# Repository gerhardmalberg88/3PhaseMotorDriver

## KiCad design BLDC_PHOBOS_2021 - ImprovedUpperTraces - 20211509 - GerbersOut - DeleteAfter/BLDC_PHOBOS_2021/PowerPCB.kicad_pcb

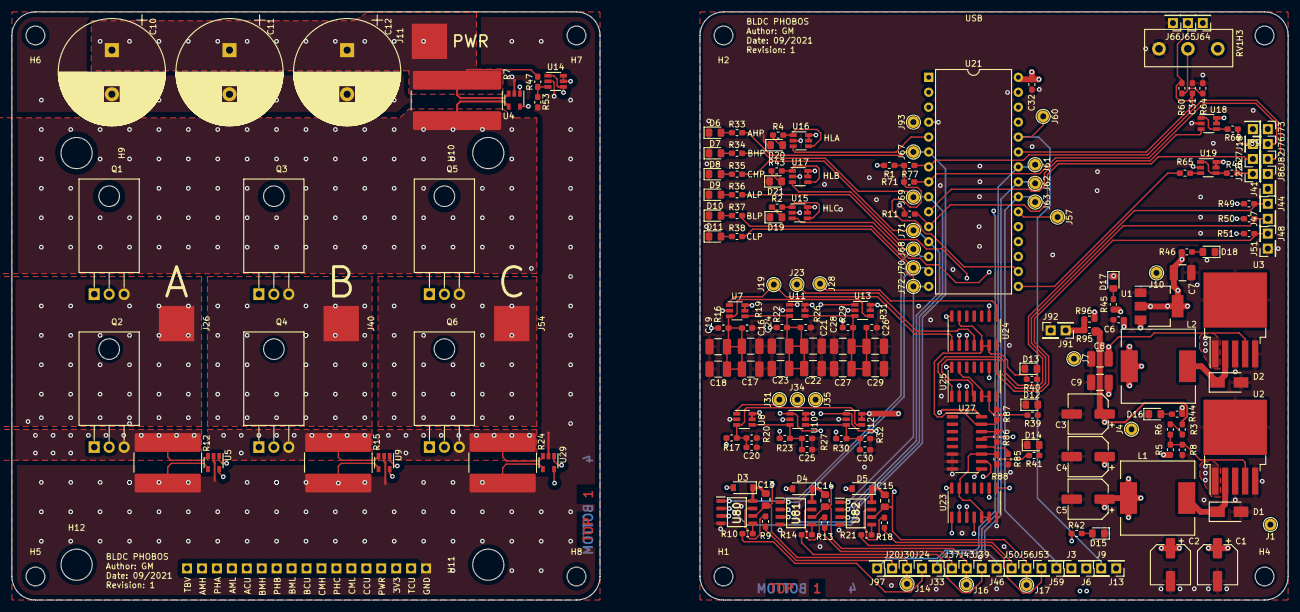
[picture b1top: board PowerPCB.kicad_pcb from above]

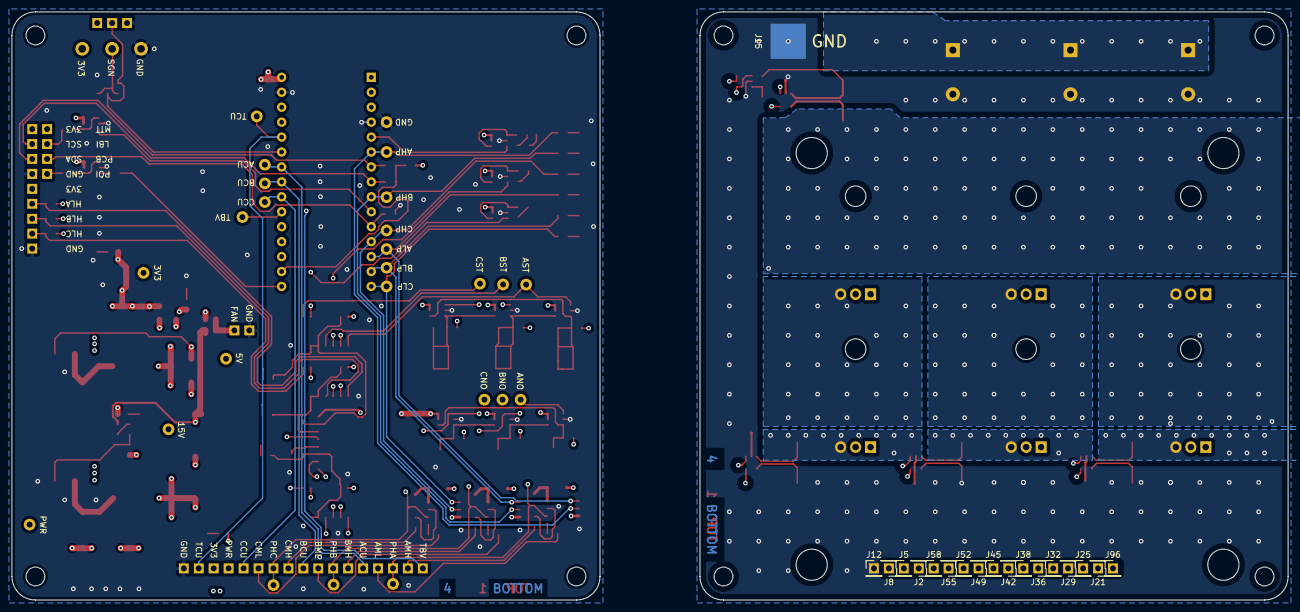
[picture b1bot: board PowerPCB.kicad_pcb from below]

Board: 4 copper layers, 100.0 x 100.0 mm, 245 parts (18 on the bottom side), 116 nets.

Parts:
C1, C2, C3, C4, C5: 100uF; CP_Elec_6.3x5.3
C6, C20, C25, C30, C31, C32: 100nF; C_0603_1608Metric_Pad1.05x0.95mm_HandSolder
C7, C8, C9, C16, C17, C18, C19, C21, C22, C23, C24, C26, C27, C28, C29: 47uF; C_1210_3225Metric_Pad1.42x2.65mm_HandSolder
C10, C11, C12: 1000uF; CP_Radial_D18.0mm_P7.50mm
C13, C14, C15: 1uF; C_0805_2012Metric_Pad1.15x1.40mm_HandSolder
D1, D2: 1A; D_SMA
D3, D4, D5: D_ALT; D_SOD-123
D6: LED_A_HIGH; LED_0805_2012Metric_Pad1.15x1.40mm_HandSolder
D7: LED_B_HIGH; LED_0805_2012Metric_Pad1.15x1.40mm_HandSolder
D8: LED_C_HIGH; LED_0805_2012Metric_Pad1.15x1.40mm_HandSolder
D9: LED_A_LOW; LED_0805_2012Metric_Pad1.15x1.40mm_HandSolder
D10: LED_B_LOW; LED_0805_2012Metric_Pad1.15x1.40mm_HandSolder
D11: LED_C_LOW; LED_0805_2012Metric_Pad1.15x1.40mm_HandSolder
D12: HALL_DATA_CONTROL; LED_0805_2012Metric_Pad1.15x1.40mm_HandSolder
D13: BEMF_START_DATA_CONTROL; LED_0805_2012Metric_Pad1.15x1.40mm_HandSolder
D14: BEMF_NORMAL_DATA_CONTROL; LED_0805_2012Metric_Pad1.15x1.40mm_HandSolder
D15: +48V LED; LED_0805_2012Metric_Pad1.15x1.40mm_HandSolder
D16: +12V LED; LED_0805_2012Metric_Pad1.15x1.40mm_HandSolder
D17: +5V LED; LED_0805_2012Metric_Pad1.15x1.40mm_HandSolder
D18: +3V3 LED; LED_0805_2012Metric_Pad1.15x1.40mm_HandSolder
D19, D20, D21: LED_HALL_BEMF; LED_0805_2012Metric_Pad1.15x1.40mm_HandSolder
H1, H2, H3, H4, H5, H6, H7, H8: MountingHole; MountingHole_3.2mm_M3
H9, H10, H11, H12: MountingHole; MountingHole_5.3mm_M5
J1: POWER+; TestPoint_THTPad_D2.0mm_Drill1.0mm
J2: 48V_From_PowerPCB; PinHeader_1x01_P2.54mm_Vertical
J3: 48V_to_Control_PCB; PinHeader_1x01_P2.54mm_Vertical
J4: +15V External; TestPoint_THTPad_D2.0mm_Drill1.0mm
J5: +3V3PowerPCB; PinHeader_1x01_P2.54mm_Vertical
J6: +3V3ControlPCB; PinHeader_1x01_P2.54mm_Vertical
J7: +5V External; TestPoint_THTPad_D2.0mm_Drill1.0mm
J8: Total_Current_Differential_PowerPCB; PinHeader_1x01_P2.54mm_Vertical
J9: Total_Current_Differential_ControlPCB; PinHeader_1x01_P2.54mm_Vertical
J10: +3V3 External; TestPoint_THTPad_D2.0mm_Drill1.0mm
J11: Con_POWER_B+; Power_Pad_6x6mm
J12: CommonGND_PowerPCB; PinHeader_1x01_P2.54mm_Vertical
J13: CommonGND_ControlPCB; PinHeader_1x01_P2.54mm_Vertical
J14: Phase_A_RAW; TestPoint_THTPad_D2.0mm_Drill1.0mm
J15: Con_POWER_GND; Power_Pad_6x6mm
J16: Phase_B_RAW; TestPoint_THTPad_D2.0mm_Drill1.0mm
J17: Phase_C_RAW; TestPoint_THTPad_D2.0mm_Drill1.0mm
J18: Low_Battery_Voltage_Indicator_Output; PinHeader_1x01_P2.54mm_Vertical
J19: Phase_A_Zero_Filtered_Start; TestPoint_THTPad_D2.0mm_Drill1.0mm
J20: A_MOS_HIGH_ControlPCB; PinHeader_1x01_P2.54mm_Vertical
J21: A_MOS_HIGH_PowerPCB; PinHeader_1x01_P2.54mm_Vertical
J22: Power_ON_Indicator_Output; PinHeader_1x01_P2.54mm_Vertical
J23: Phase_B_Zero_Filtered_Start; TestPoint_THTPad_D2.0mm_Drill1.0mm
J24: A_MOS_LOW_ControlPCB; PinHeader_1x01_P2.54mm_Vertical
J25: Phase_A_PowerPCB; PinHeader_1x01_P2.54mm_Vertical
J26: Connector_A; Power_Pad_6x6mm
J27: Program&Control_Button; PinHeader_1x01_P2.54mm_Vertical
J28: Phase_C_Zero_Filtered_Start; TestPoint_THTPad_D2.0mm_Drill1.0mm
J29: A_MOS_LOW_PowerPCB; PinHeader_1x01_P2.54mm_Vertical
J30: Phase_A_ControlPCB; PinHeader_1x01_P2.54mm_Vertical
J31: Phase_A_Zero_Filtered_Normal; TestPoint_THTPad_D2.0mm_Drill1.0mm
J32: A_Shunt+_PowerPCB; PinHeader_1x01_P2.54mm_Vertical
J33: A_Shunt+_ControlPCB; PinHeader_1x01_P2.54mm_Vertical
J34: Phase_B_Zero_Filtered_Normal; TestPoint_THTPad_D2.0mm_Drill1.0mm
J35: Phase_C_Zero_Filtered_Normal; TestPoint_THTPad_D2.0mm_Drill1.0mm
J36: B_MOS_HIGH_PowerPCB; PinHeader_1x01_P2.54mm_Vertical
J37: B_MOS_HIGH_ControlPCB; PinHeader_1x01_P2.54mm_Vertical
J38: Phase_B_PowerPCB; PinHeader_1x01_P2.54mm_Vertical
J39: B_MOS_LOW_ControlPCB; PinHeader_1x01_P2.54mm_Vertical
J40: Connector_B; Power_Pad_6x6mm
J41: Hall +3V3; PinHeader_1x01_P2.54mm_Vertical
J42: B_MOS_LOW_PowerPCB; PinHeader_1x01_P2.54mm_Vertical
J43: Phase_B_ControlPCB; PinHeader_1x01_P2.54mm_Vertical
J44: Con_HALL_A; PinHeader_1x01_P2.54mm_Vertical
J45: B_Shunt+_PowerPCB; PinHeader_1x01_P2.54mm_Vertical
J46: B_Shunt+_ControlPCB; PinHeader_1x01_P2.54mm_Vertical
J47: Con_HALL_B; PinHeader_1x01_P2.54mm_Vertical
J48: Con_HALL_C; PinHeader_1x01_P2.54mm_Vertical
J49: C_MOS_HIGH_PowerPCB; PinHeader_1x01_P2.54mm_Vertical
J50: C_MOS_HIGH_ControlPCB; PinHeader_1x01_P2.54mm_Vertical
J51: Hall GND; PinHeader_1x01_P2.54mm_Vertical
J52: Phase_C_PowerPCB; PinHeader_1x01_P2.54mm_Vertical
J53: C_MOS_LOW_ControlPCB; PinHeader_1x01_P2.54mm_Vertical
J54: Connector_C; Power_Pad_6x6mm
J55: C_MOS_LOW_PowerPCB; PinHeader_1x01_P2.54mm_Vertical
J56: Phase_C_ControlPCB; PinHeader_1x01_P2.54mm_Vertical
J57: Voltage Sense SGN; TestPoint_THTPad_D2.0mm_Drill1.0mm
J58: C_Shunt+_PowerPCB; PinHeader_1x01_P2.54mm_Vertical
J59: C_Shunt+_ControlPCB; PinHeader_1x01_P2.54mm_Vertical
J60: Total_Battery_Current; TestPoint_THTPad_D2.0mm_Drill1.0mm
J61: A_Low_Side_Current_ADC; TestPoint_THTPad_D2.0mm_Drill1.0mm
J62: B_Low_Side_Current_ADC; TestPoint_THTPad_D2.0mm_Drill1.0mm
J63: C_Low_Side_Current_ADC; TestPoint_THTPad_D2.0mm_Drill1.0mm
J64: Throttle 3V3; PinHeader_1x01_P2.54mm_Vertical
J65: Throttle Signal; PinHeader_1x01_P2.54mm_Vertical
J66: Throttle GND; PinHeader_1x01_P2.54mm_Vertical
J67: A_HIGH_MCU; TestPoint_THTPad_D2.0mm_Drill1.0mm
J68: A_LOW_MCU; TestPoint_THTPad_D2.0mm_Drill1.0mm
J69: B_HIGH_MCU; TestPoint_THTPad_D2.0mm_Drill1.0mm
J70: B_LOW_MCU; TestPoint_THTPad_D2.0mm_Drill1.0mm
J71: C_HIGH_MCU; TestPoint_THTPad_D2.0mm_Drill1.0mm
J72: C_LOW_MCU; TestPoint_THTPad_D2.0mm_Drill1.0mm
J73: I2C 3V3; PinHeader_1x01_P2.54mm_Vertical
J76: I2C_SCL; PinHeader_1x01_P2.54mm_Vertical
J82: I2C_SDA; PinHeader_1x01_P2.54mm_Vertical
J86: I2C GND; PinHeader_1x01_P2.54mm_Vertical
J89: Motor_Temp; PinHeader_1x01_P2.54mm_Vertical
J91: FAN_PWR; PinHeader_1x01_P2.54mm_Vertical
J92: FAN_GND; PinHeader_1x01_P2.54mm_Vertical
J93: GND_Extra; TestPoint_THTPad_D2.0mm_Drill1.0mm
J96: Total_Voltage_PowerPCB; PinHeader_1x01_P2.54mm_Vertical
J97: Total_Voltage_ControlPCB; PinHeader_1x01_P2.54mm_Vertical
L1: 270uH 2.1A; L_Wuerth_WE-PD-Typ-LS
L2: 33uH 3.6A; L_Wuerth_WE-PD-Typ-LS
Q1, Q2, Q3, Q4, Q5, Q6: IRFB3006; TO-220-3_Horizontal_TabDown
R1, R5, R65, R95, R96: 0R; R_0603_1608Metric_Pad1.05x0.95mm_HandSolder
R2, R4, R42, R43, R48, R69: 4.7k; R_0603_1608Metric_Pad1.05x0.95mm_HandSolder
R3, R11, R19, R20, R26, R27, R31, R32, R49, R50, R51, R60, R71, R77, R85, R86, R87, R88: 10k; R_0603_1608Metric_Pad1.05x0.95mm_HandSolder
R6, R8, R33, R34, R35, R36, R37, R38, R39, R40, R41, R44, R45, R46, R53: 1k; R_0603_1608Metric_Pad1.05x0.95mm_HandSolder
R7: 1m; Triple_R_2816_7142Metric_Pad3.20x4.45mm_Handsoldered - Copy
R9, R10, R13, R14, R18, R21: 100; R_0603_1608Metric_Pad1.05x0.95mm_HandSolder
R12, R15, R24: 1m; Parallel_R_2816_7142Metric_Pad3.20x4.45mm_Handsoldered
R16, R17, R22, R23, R29, R30: 100k; R_0603_1608Metric_Pad1.05x0.95mm_HandSolder
R47: 20k; R_0603_1608Metric_Pad1.05x0.95mm_HandSolder
R64: 200k; R_0603_1608Metric_Pad1.05x0.95mm_HandSolder
RV1: R_POT; Potentiometer_PUMLINPartco
U1: LD1117S33TR_SOT223; SOT-223-3_TabPin2
U2: LM2576HVS-ADJ_NOPB_NOPB_TO_263_TAB3GND; TO-263-5_TabPin3
U3: LM2596SX-5.0_NOPB; TO-263-5_TabPin3
U4, U5, U9, U29: INA195; SOT-23-5
U7, U8, U10, U11, U12, U13, U14, U15, U16, U17, U18, U19: LMH6618; TSOT-23-6
U21: STM32F303K8Tx_NUCLEO-F303K8; DIP-30_W15.24mm
U23, U24, U25: 4066; SOIC-14_3.9x8.7mm_P1.27mm
U27: 4052; SOIC-16_3.9x9.9mm_P1.27mm
U80, U81, U82: L6395D; SOIC127P600X175-8N

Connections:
3V3_MCU_Output: R1.1, R71.1, R77.1, U21.17
+3V3: C7.2, J6.1, J10.1, J41.1, J64.1, J73.1, R1.2, R46.2, R49.2, R50.2, R51.2, RV1.1, U1.2, U7.5, U7.6, U8.5, U8.6, U10.5, U10.6, U11.5, U11.6, U12.5, U12.6, U13.5, U13.6, U15.5, U15.6, U16.5, U16.6, U17.5, U17.6, U23.14, U24.14, U25.14, U27.13, U27.16
+3V3PowerPCB: J5.1, U4.5, U5.5, U9.5, U14.5, U14.6, U29.5
+5V: C6.2, C8.2, C9.2, C32.2, J7.1, L2.2, R45.2, R96.2, U1.3, U3.4, U18.5, U18.6, U19.5, U19.6, U21.30
+15V: C3.1, C4.1, C5.1, D3.2, D4.2, D5.2, J4.1, L1.2, R3.1, R5.2, R44.2, R95.1, U3.1, U80.3, U81.3, U82.3
+48V: J2.1, Q1.2, Q3.2, Q5.2, R7.2, U4.4
A_HIGH_Side_PWM: J67.1, R33.2, U21.6, U80.2
A_LOW_Side_PWM: J68.1, R36.2, U21.13, U80.1
A_Low_Side_Current_ADC: J33.1, J61.1, U21.24
A_MOS_HIGH_ControlPCB: R9.2, U80.7
A_MOS_HIGH_PowerPCB: J21.1, Q1.1
A_MOS_LOW_ControlPCB: R10.2, U80.5
A_MOS_LOW_PowerPCB: J29.1, Q2.1
A_Shunt+_PowerPCB: Q2.3, R12.1, U5.3
B_HIGH_Side_PWM: J69.1, R34.2, U21.9, U81.2
B_LOW_Side_PWM: J70.1, R37.2, U21.14, U81.1
B_Low_Side_Current_ADC: J46.1, J62.1, U21.23
B_MOS_HIGH_ControlPCB: R13.2, U81.7
B_MOS_HIGH_PowerPCB: J36.1, Q3.1
B_MOS_LOW_ControlPCB: R14.2, U81.5
B_MOS_LOW_PowerPCB: J42.1, Q4.1
B_Shunt+_PowerPCB: Q4.3, R15.1, U9.3
Bemf_Normal_Data_Control: R41.2, R88.1, U23.5, U23.6, U23.13, U27.11
Bemf_Start_Data_Control: R40.2, R87.1, U24.5, U24.6, U24.13, U27.15
C_HIGH_Side_PWM: J71.1, R35.2, U21.12, U82.2
C_LOW_Side_PWM: J72.1, R38.2, U21.15, U82.1
C_Low_Side_Current_ADC: J59.1, J63.1, U21.22
C_MOS_HIGH_ControlPCB: R18.2, U82.7
C_MOS_HIGH_PowerPCB: J49.1, Q5.1
C_MOS_LOW_ControlPCB: R21.2, U82.5
C_MOS_LOW_PowerPCB: J55.1, Q6.1
C_Shunt+_PowerPCB: Q6.3, R24.1, U29.3
FAN_PWR: J91.1, R95.2, R96.1
GND: C1.2, C2.2, C3.2, C4.2, C5.2, C6.1, C7.1, C8.1, C9.1, C10.2, C11.2, C12.2, C16.1, C17.1, C18.1, C19.1, C20.1, C21.1, C22.1, C23.1, C24.1, C25.1, C26.1, C27.1, C28.1, C29.1, C30.1, C31.1, C32.1, D1.2, D2.2, D6.1, D7.1, D8.1, D9.1, D10.1, D11.1, D12.1, D13.1, D14.1, D15.1, D16.1, D17.1, D18.1, D19.1, D20.1, D21.1, J12.1, J13.1, J15.1, J51.1, J66.1, J86.1, J92.1, J93.1, R8.2, R11.2, R12.2, R15.2, R19.2, R20.2, R24.2, R26.2, R27.2, R31.2, R32.2, R53.2, R64.2, R85.2, R86.2, R87.2, R88.2, RV1.3, U1.1, U2.3, U2.5, U3.3, U3.5, U4.2, U5.2, U5.4, U7.2, U8.2, U9.2, U9.4, U10.2, U11.2, U12.2, U13.2, U14.2, U15.2, U16.2, U17.2, U18.2, U19.2, U21.4, U21.29, U23.7, U24.7, U25.7, U27.6, U27.7, U27.8, U29.2, U29.4, U80.4, U81.4, U82.4
Hall_A: J44.1, R49.1, U25.1
Hall_B: J47.1, R50.1, U25.4
Hall_Bemf_A: U16.3, U21.5, U23.2, U24.2, U25.2
Hall_Bemf_B: U17.3, U21.20, U23.3, U24.3, U25.3
Hall_Bemf_C: U15.3, U21.19, U23.9, U24.9, U25.9
Hall_C: J48.1, R51.1, U25.8
Hall_Data_Control: R39.2, R86.1, U25.5, U25.6, U25.13, U27.14
Hall_Mux_1_Digital_Write: U21.1, U27.10
Hall_Mux_2_Digital_Write: U21.2, U27.9
I2C_SCL: J76.1, R71.2, U21.8
I2C_SDA: J82.1, R77.2, U21.7
Low_Battery_Voltage_Indicator: U18.3, U21.10
Low_Battery_Voltage_Indicator_Output: J18.1, R69.1
unnamed: C10.1, C11.1, C12.1, J11.1, R7.1, R47.1, U4.3
unnamed: C13.1, D3.1, U80.8
unnamed: C14.1, D4.1, U81.8
unnamed: C15.1, D5.1, U82.8
unnamed: D1.1, L1.1, U2.2
unnamed: D2.1, L2.1, U3.2
unnamed: D6.2, R33.1
unnamed: D7.2, R34.1
unnamed: D8.2, R35.1
unnamed: D9.2, R36.1
unnamed: D10.2, R37.1
unnamed: D11.2, R38.1
unnamed: D12.2, R39.1
unnamed: D13.2, R40.1
unnamed: D14.2, R41.1
unnamed: D15.2, R42.1
unnamed: D16.2, R44.1
unnamed: D17.2, R45.1
unnamed: D18.2, R46.1
unnamed: D19.2, R2.1
unnamed: D20.2, R4.1
unnamed: D21.2, R43.1
unnamed: J8.1, U4.1
unnamed: J20.1, R9.1
unnamed: J24.1, R10.1
unnamed: J32.1, U5.1
unnamed: J37.1, R13.1
unnamed: J39.1, R14.1
unnamed: J45.1, U9.1
unnamed: J50.1, R18.1
unnamed: J53.1, R21.1
unnamed: J58.1, U29.1
unnamed: R2.2, U15.1, U15.4
unnamed: R3.2, R6.1
unnamed: R4.2, U16.1, U16.4
unnamed: R5.1, R6.2, R8.1, U2.4
unnamed: R43.2, U17.1, U17.4
unnamed: R47.2, R53.1, U14.3
unnamed: R48.2, U19.1, U19.4
unnamed: R60.2, R64.1, RV1.2
unnamed: R65.1, U19.3
unnamed: R69.2, U18.1, U18.4
unnamed: R85.1, U27.12
Normal_Phase_A_Filtered: C20.2, R17.2, R20.1, U8.3, U12.4
Normal_Phase_B_Filtered: C25.2, R23.2, R27.1, U8.4, U10.3
Normal_Phase_C_Filtered: C30.2, R30.2, R32.1, U10.4, U12.3
Phase_A_ControlPCB: C13.2, J14.1, J30.1, R16.1, R17.1, U80.6
Phase_A_Emf_Zero_Normal: J31.1, U8.1, U23.1
Phase_A_Emf_Zero_Start: J19.1, U7.1, U24.1
Phase_A_PowerPCB: J25.1, J26.1, Q1.3, Q2.2
Phase_B_ControlPCB: C14.2, J16.1, J43.1, R22.1, R23.1, U81.6
Phase_B_Emf_Zero_Normal: J34.1, U10.1, U23.4
Phase_B_Emf_Zero_Start: J23.1, U11.1, U24.4
Phase_B_PowerPCB: J38.1, J40.1, Q3.3, Q4.2
Phase_C_ControlPCB: C15.2, J17.1, J56.1, R29.1, R30.1, U82.6
Phase_C_Emf_Zero_Normal: J35.1, U12.1, U23.8
Phase_C_Emf_Zero_Start: J28.1, U13.1, U24.8
Phase_C_PowerPCB: J52.1, J54.1, Q5.3, Q6.2
Power_Main: C1.1, C2.1, J1.1, J3.1, R42.2, U2.1
Power_ON_Indicator: R65.2, U21.16
Power_ON_Indicator_Output: J22.1, R48.1
Program&Control_Button: J27.1, R11.1, U21.11
Start_Phase_A_Filtered: C16.2, C17.2, C18.2, C19.2, R16.2, R19.1, U7.3, U13.4
Start_Phase_B_Filtered: C21.2, C22.2, C23.2, C24.2, R22.2, R26.1, U7.4, U11.3
Start_Phase_C_Filtered: C26.2, C27.2, C28.2, C29.2, R29.2, R31.1, U11.4, U13.3
Throttle_ADC: C31.2, J65.1, R60.1, U21.25
Total_Battery_Current: J9.1, J60.1, U21.26
Total_Battery_Voltage: J57.1, J97.1, U21.21
Total_Battery_Voltage_PowerPCB: J96.1, U14.1, U14.4

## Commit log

2021-09-04 Added Initial KiCAD
2021-09-06 Updated Design
2021-09-15 Updated Layout Added silkscreens
2021-09-17 UpdatedDesign
